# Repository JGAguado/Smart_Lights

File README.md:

[![GitHub Release][releases-shield]][releases]
[![License][license-shield]](LICENSE)
[![BuyIt][buyit-shield]][tindie]

[![Project Maintenance][maintenance-shield]][maintenance]
[![BuyMeCoffee][buymecoffee-shield]][buymecoffee]

# Smart Lights X4
The Smart Lights X4 is an ESP32 based board for controlling up to 4 dimmeable 12V led strips, ready to input 230VAC or 12VDC.

## Project tree

<li><a href="./Design/">Design</a></li>
<li><a href="./Documentation/">Documentation</a></li>

<li><a href="./README.md">README.md</a></li>

[releases-shield]: https://img.shields.io/github/release/JGAguado/Smart_Lights.svg?style=for-the-badge
[releases]: https://github.com/JGAguado/Smart_Lights/releases

[license-shield]: https://img.shields.io/badge/License-CC%20BY--NC--SA%204.0-lightgrey.svg?style=for-the-badge

[maintenance-shield]: https://img.shields.io/badge/maintainer-J.%20G.%20Aguado-blue.svg?style=for-the-badge
[maintenance]: https://github.com/JGAguado

[buymecoffee-shield]: https://img.shields.io/badge/buy%20me%20a%20coffee-support-yellow.svg?style=for-the-badge&logo=buymeacoffee
[buymecoffee]: https://www.buymeacoffee.com/J.G.Aguado

[buyit-shield]: https://img.shields.io/badge/get%20it%20on-tindie-247d84.svg?style=for-the-badge
[tindie]: https://www.tindie.com/products/themakerllama/smart-lights-x4/

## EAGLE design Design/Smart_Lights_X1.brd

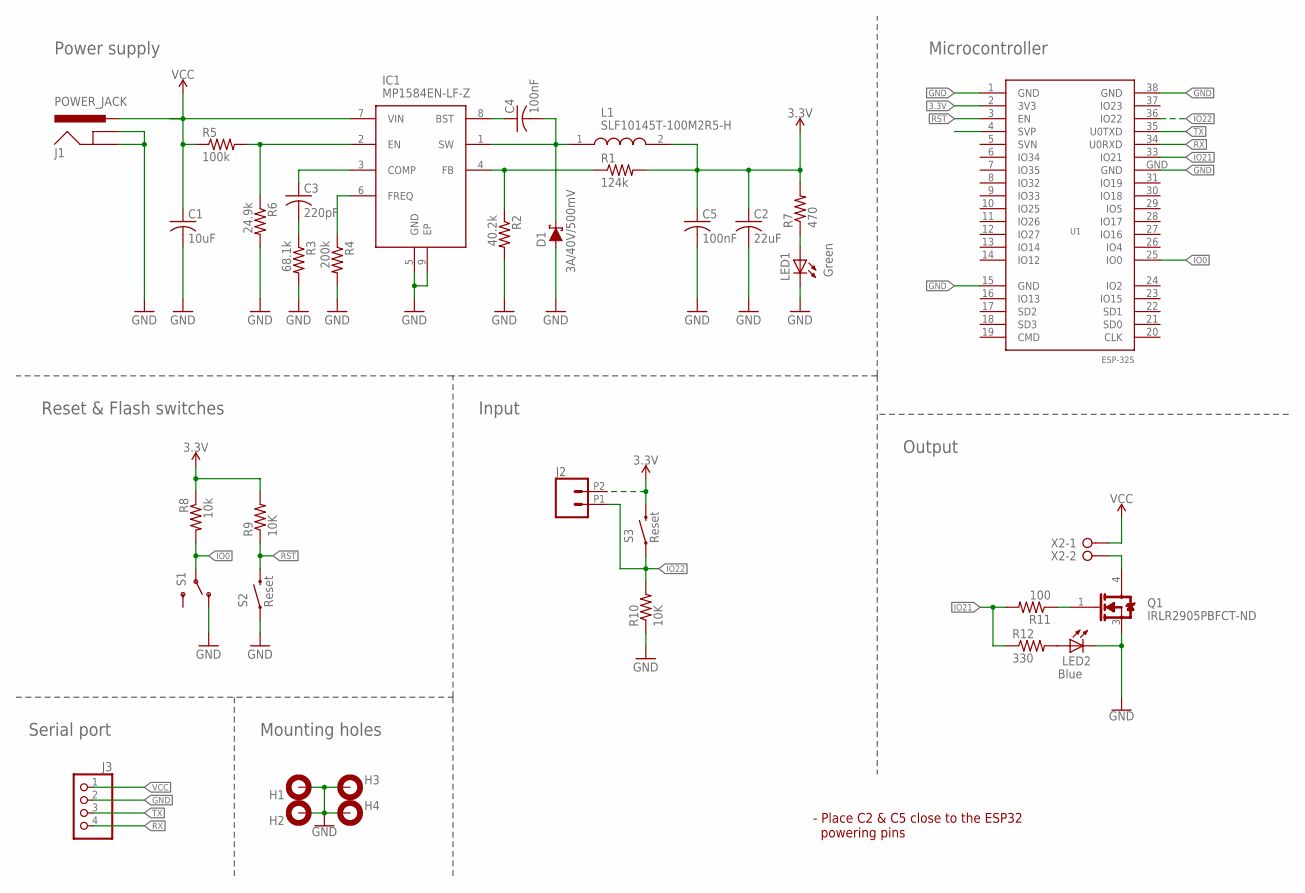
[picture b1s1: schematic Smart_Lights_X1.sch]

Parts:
C1: 10uF; C1206
C2: 22uF; C1206
C3: 220pF; C1206
C4, C5: 100nF; C1206
D1: 3A/40V/500mV; SMA-DIODE
H1, H2, H3, H4: MOUNT-PAD-ROUND; 3,0-PAD
IC1: MP1584EN-LF-Z; SOIC127P600X170-9N
J1: POWER_JACK; POWER_JACK_PTH
J2: CONN_022.54MM_SCREWTERM; 1X02_2.54_SCREWTERM
J3: PINHD-1X4; 1X04
L1: SLF10145T-100M2R5-H; SLF10145
LED1: Green; LED1206
LED2: Blue; LED1206
Q1: IRLR2905TRPBF; INFINEON_TECHNOLOGIES_IRLR2905TRPBF_0
R1: 124k; M1206
R2: 40.2k; M1206
R3: 68.1k; M1206
R4: 200k; M1206
R5: 100k; M1206
R6: 24.9k; M1206
R7: 470; M1206
R8: 10k; M1206
R9, R10: 10K; M1206
R11: 100; M1206
R12: 330; M1206
S1: SWITCH_SPDT; KPS-1290
S2, S3: Reset; TACTILE_SWITCH_TALL
U1: ESP-32S
X2: W237-02P; W237-132

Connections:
3.3V: C2.1, C5.1, J2.P2 (2), L1.2, R1.2, R7.2, R8.1, R9.2, S3.B2 (2), U1.2 (3V3)
GND: C1.2, C2.2, C5.2, D1.A, H1.B3,0, H1.P$2, H1.P$3, H1.P$4, H1.P$5, H1.P$6, H1.P$7, H1.P$8, H1.P$9, H2.B3,0, H2.P$2, H2.P$3, H2.P$4, H2.P$5, H2.P$6, H2.P$7, H2.P$8, H2.P$9, H3.B3,0, H3.P$2, H3.P$3, H3.P$4, H3.P$5, H3.P$6, H3.P$7, H3.P$8, H3.P$9, H4.B3,0, H4.P$2, H4.P$3, H4.P$4, H4.P$5, H4.P$6, H4.P$7, H4.P$8, H4.P$9, IC1.5 (GND), IC1.9 (EP), J1.GND, J1.GNDBREAK, J3.2, LED1.C, LED2.C, Q1.3 (SOURCE), R2.2, R3.2, R4.2, R6.2, R10.1, S1.O, S2.A2 (1), U1.1 (GND), U1.15 (GND), U1.38 (GND), U1.GND
IN_5: U1.4 (SVP)
IO0: R8.2, S1.P, U1.25 (IO0)
IO21: R11.2, R12.1, U1.33 (IO21)
IO22: J2.P1 (1), R10.2, S3.A2 (1), U1.36 (IO22)
unnamed: C4.1, IC1.8 (BST)
unnamed: C4.2, D1.C, IC1.1 (SW), L1.1
unnamed: Q1.4 (DRAIN), X2.2
unnamed: Q1.1 (GATE), R11.1
unnamed: IC1.4 (FB), R1.1, R2.1
unnamed: C3.2, R3.1
unnamed: C3.1, IC1.3 (COMP)
unnamed: IC1.6 (FREQ), R4.1
unnamed: IC1.2 (EN), R5.2, R6.1
unnamed: LED1.A, R7.1
unnamed: LED2.A, R12.2
RST: R9.1, S2.B2 (2), U1.3 (EN)
RX: J3.4, U1.34 (U0RXD)
TX: J3.3, U1.35 (U0TXD)
VCC: C1.1, IC1.7 (VIN), J1.PWR, J3.1, R5.1, X2.1

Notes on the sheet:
Reset & Flash switches
- Place C2 & C5 close to the ESP32 powering pins
Input
Output
Serial port
Mounting holes
Microcontroller
Power supply

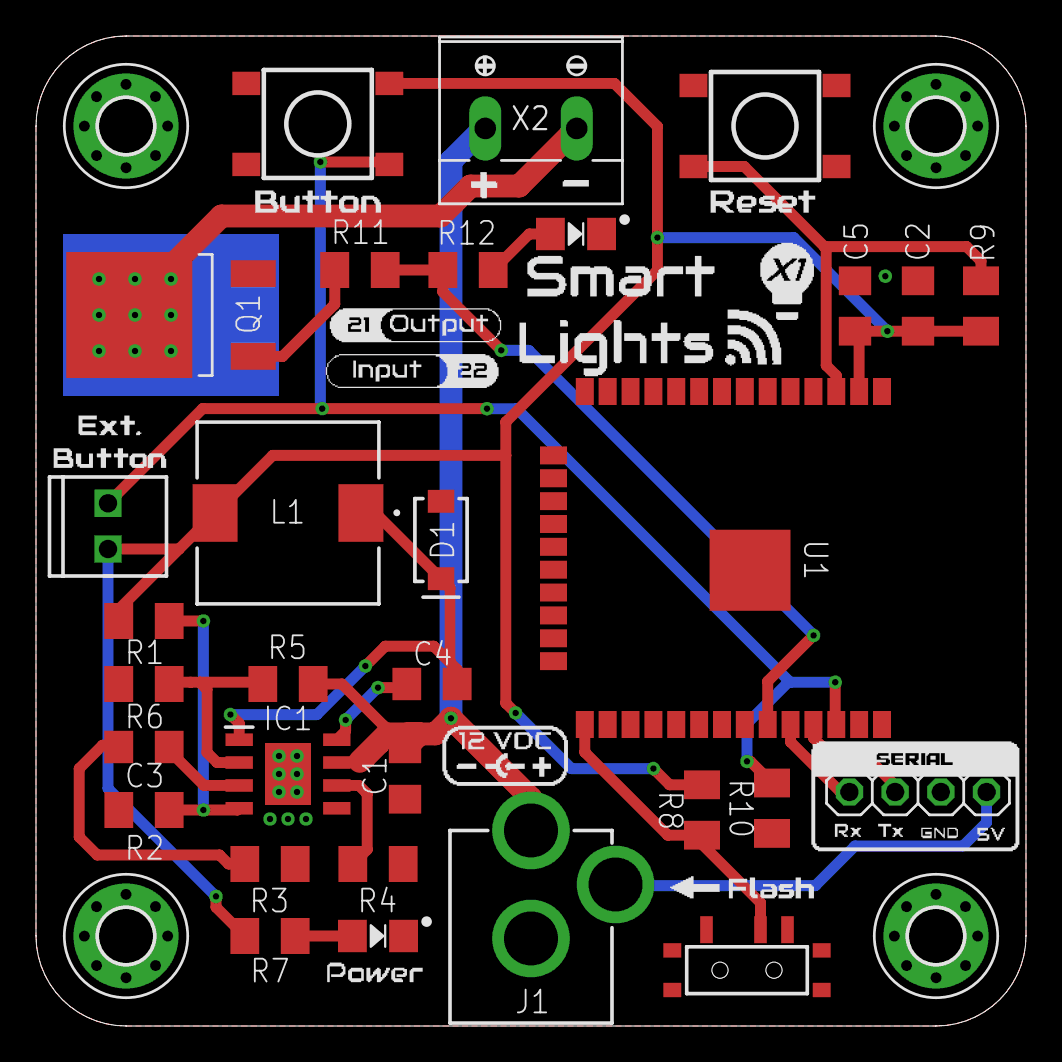
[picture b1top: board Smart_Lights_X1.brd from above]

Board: 2 copper layers, 55.0 x 55.0 mm, 35 parts (0 on the bottom side), 20 nets.

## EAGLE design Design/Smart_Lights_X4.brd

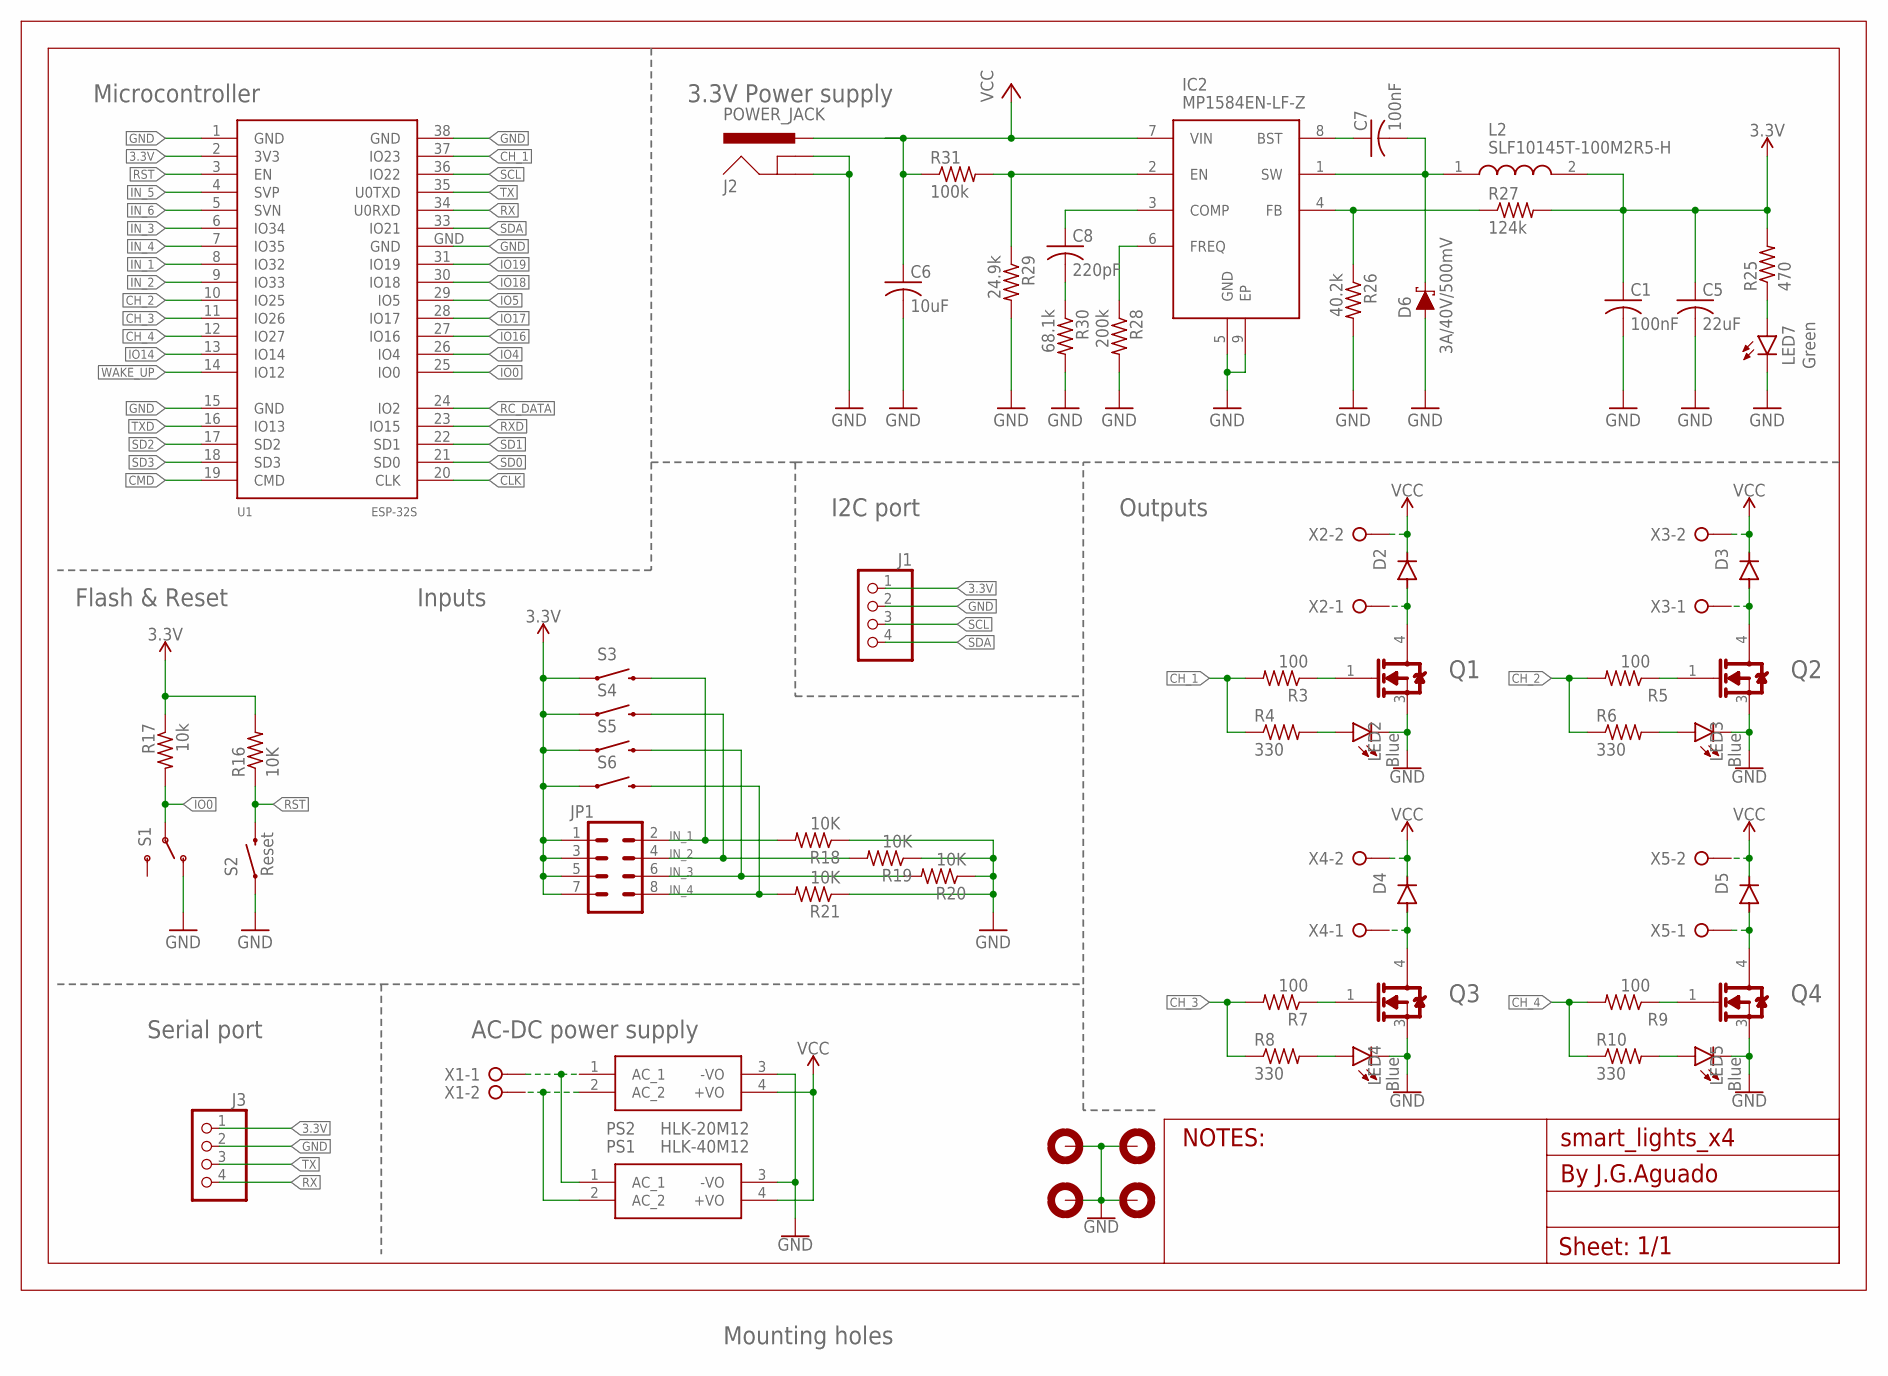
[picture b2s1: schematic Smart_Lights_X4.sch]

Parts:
C1, C7: 100nF; C0603
C5: 22uF; C0603
C6: 10uF; C0603
C8: 220pF; C0603
D2, D3, D4, D5: DIODE-SOD123; SOD123
D6: 3A/40V/500mV; SMA-DIODE
FRAME1: A4L-LOC; 92X87
IC2: MP1584EN-LF-Z; SOIC127P600X170-9N
J1, J3: PINHD-1X4; 1X04
J2: POWER_JACK; POWER_JACK_PTH
JP1: CONN_04X2; 2X4
L2: SLF10145T-100M2R5-H; SLF10145
LED2, LED3, LED4, LED5: Blue; SML0603
LED7: Green; SML0603
PS1: HLK-40M12
PS2: HLK-20M12
Q1, Q2, Q3, Q4: IRLR2905TRPBF; INFINEON_TECHNOLOGIES_IRLR2905TRPBF_0
R3, R5, R7, R9: 100; R0603
R4, R6, R8, R10: 330; R0603
R16, R18, R19, R20, R21: 10K; R0603
R17: 10k; R0603
R25: 470; R0603
R26: 40.2k; R0603
R27: 124k; R0603
R28: 200k; R0603
R29: 24.9k; R0603
R30: 68.1k; R0603
R31: 100k; R0603
S1: SWITCH_SPDT; KPS-1290
S2, S3, S4, S5, S6: Reset; TACTILE_SWITCH_TALL
U1: ESP-32S
X1, X2, X3, X4, X5: W237-02P; W237-132

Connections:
3.3V: C1.1, C5.1, J1.1, J3.1, JP1.1, JP1.3, JP1.5, JP1.7, L2.2, R16.2, R17.1, R25.2, R27.2, S3.A2 (1), S4.A2 (1), S5.A2 (1), S6.A2 (1), U1.2 (3V3)
CH_1: R3.2, R4.1, U1.37 (IO23)
CH_2: R5.2, R6.1, U1.10 (IO25)
CH_3: R7.2, R8.1, U1.11 (IO26)
CH_4: R9.2, R10.1, U1.12 (IO27)
CLK: U1.20 (CLK)
CMD: U1.19 (CMD)
GND: C1.2, C5.2, C6.2, D6.A, FRAME1.B3,1 (MOUNT), FRAME1.B3,2 (MOUNT1), FRAME1.B3,3 (MOUNT2), FRAME1.B3,6 (MOUNT3), IC2.5 (GND), IC2.9 (EP), J1.2, J2.GND, J2.GNDBREAK, J3.2, LED2.C, LED3.C, LED4.C, LED5.C, LED7.C, PS1.3 (-VO), PS2.3 (-VO), Q1.3 (SOURCE), Q2.3 (SOURCE), Q3.3 (SOURCE), Q4.3 (SOURCE), R18.1, R19.1, R20.1, R21.1, R26.2, R28.2, R29.2, R30.2, S1.O, S2.A2 (1), U1.1 (GND), U1.15 (GND), U1.38 (GND), U1.GND
IN_1: JP1.2, R18.2, S3.B2 (2), U1.8 (IO32)
IN_2: JP1.4, R19.2, S4.B2 (2), U1.9 (IO33)
IN_3: JP1.6, R20.2, S5.B2 (2), U1.6 (IO34)
IN_4: JP1.8, R21.2, S6.B2 (2), U1.7 (IO35)
IN_5: U1.4 (SVP)
IN_6: U1.5 (SVN)
IO0: R17.2, S1.P, U1.25 (IO0)
IO4: U1.26 (IO4)
IO5: U1.29 (IO5)
IO14: U1.13 (IO14)
IO16: U1.27 (IO16)
IO17: U1.28 (IO17)
IO18: U1.30 (IO18)
IO19: U1.31 (IO19)
unnamed: Q2.1 (GATE), R5.1
unnamed: PS1.1 (AC_1), PS2.1 (AC_1), X1.1
unnamed: PS1.2 (AC_2), PS2.2 (AC_2), X1.2
unnamed: D2.A, Q1.4 (DRAIN), X2.1
unnamed: Q1.1 (GATE), R3.1
unnamed: D3.A, Q2.4 (DRAIN), X3.1
unnamed: Q3.1 (GATE), R7.1
unnamed: D4.A, Q3.4 (DRAIN), X4.1
unnamed: Q4.1 (GATE), R9.1
unnamed: D5.A, Q4.4 (DRAIN), X5.1
unnamed: LED4.A, R8.2
unnamed: LED2.A, R4.2
unnamed: LED3.A, R6.2
unnamed: LED5.A, R10.2
unnamed: LED7.A, R25.1
unnamed: C7.1, IC2.8 (BST)
unnamed: C7.2, D6.C, IC2.1 (SW), L2.1
unnamed: IC2.4 (FB), R26.1, R27.1
unnamed: C8.2, R30.1
unnamed: C8.1, IC2.3 (COMP)
unnamed: IC2.6 (FREQ), R28.1
unnamed: IC2.2 (EN), R29.1, R31.2
RC_DATA: U1.24 (IO2)
RST: R16.1, S2.B2 (2), U1.3 (EN)
RX: J3.4, U1.34 (U0RXD)
RXD: U1.23 (IO15)
SCL: J1.3, U1.36 (IO22)
SD0: U1.21 (SD0)
SD1: U1.22 (SD1)
SD2: U1.17 (SD2)
SD3: U1.18 (SD3)
SDA: J1.4, U1.33 (IO21)
TX: J3.3, U1.35 (U0TXD)
TXD: U1.16 (IO13)
VCC: C6.1, D2.C, D3.C, D4.C, D5.C, IC2.7 (VIN), J2.PWR, PS1.4 (+VO), PS2.4 (+VO), R31.1, X2.2, X3.2, X4.2, X5.2
WAKE_UP: U1.14 (IO12)

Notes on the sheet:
Microcontroller
3.3V Power supply
Flash & Reset
Inputs
Outputs
Mounting holes
Serial port
AC-DC power supply
I2C port

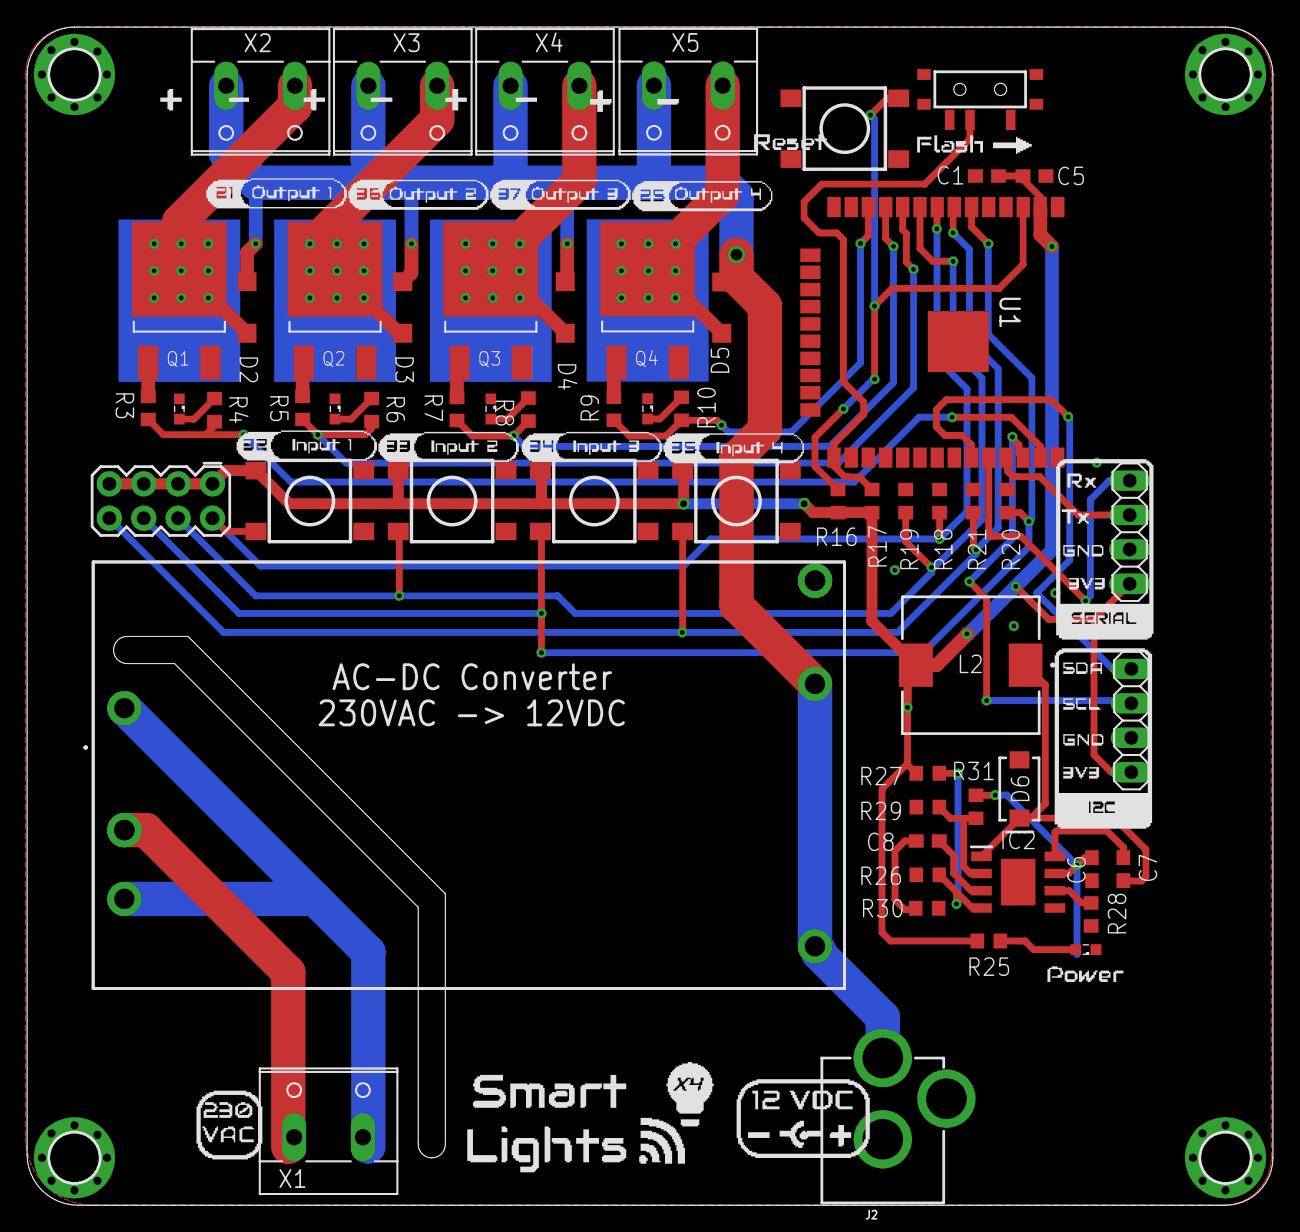
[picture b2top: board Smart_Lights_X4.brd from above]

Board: 2 copper layers, 92.0 x 87.0 mm, 61 parts (0 on the bottom side), 39 nets.

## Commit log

2022-04-13 Added silkscreen design
2022-04-13 Added design files
2022-04-13 Added documentation
2022-04-13 First commit to X4 branch
2022-04-13 Added silkscreen
2022-04-24 Added Documentation/Images
2022-04-24 Updated Documentation/Images
2022-04-24 Updated silkscreen
2022-05-11 Updated documentation adding Measures.pdf and Datasheets
2022-05-14 Added some images
2022-05-16 Updated documentation
2022-05-23 Fixed DC Jack connection
2022-05-29 Resize dimensions to fit in the 92x87 enclosure
2022-05-29 C2 & C5 Grounded

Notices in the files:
parts and their libraries:
esp32: Creative Commons Attribution-ShareAlike 4.0 International
SparkFun-Retired: Licensing: Creative Commons ShareAlike 4.0 International - https://creativecommons.org/licenses/by-sa/4.0
